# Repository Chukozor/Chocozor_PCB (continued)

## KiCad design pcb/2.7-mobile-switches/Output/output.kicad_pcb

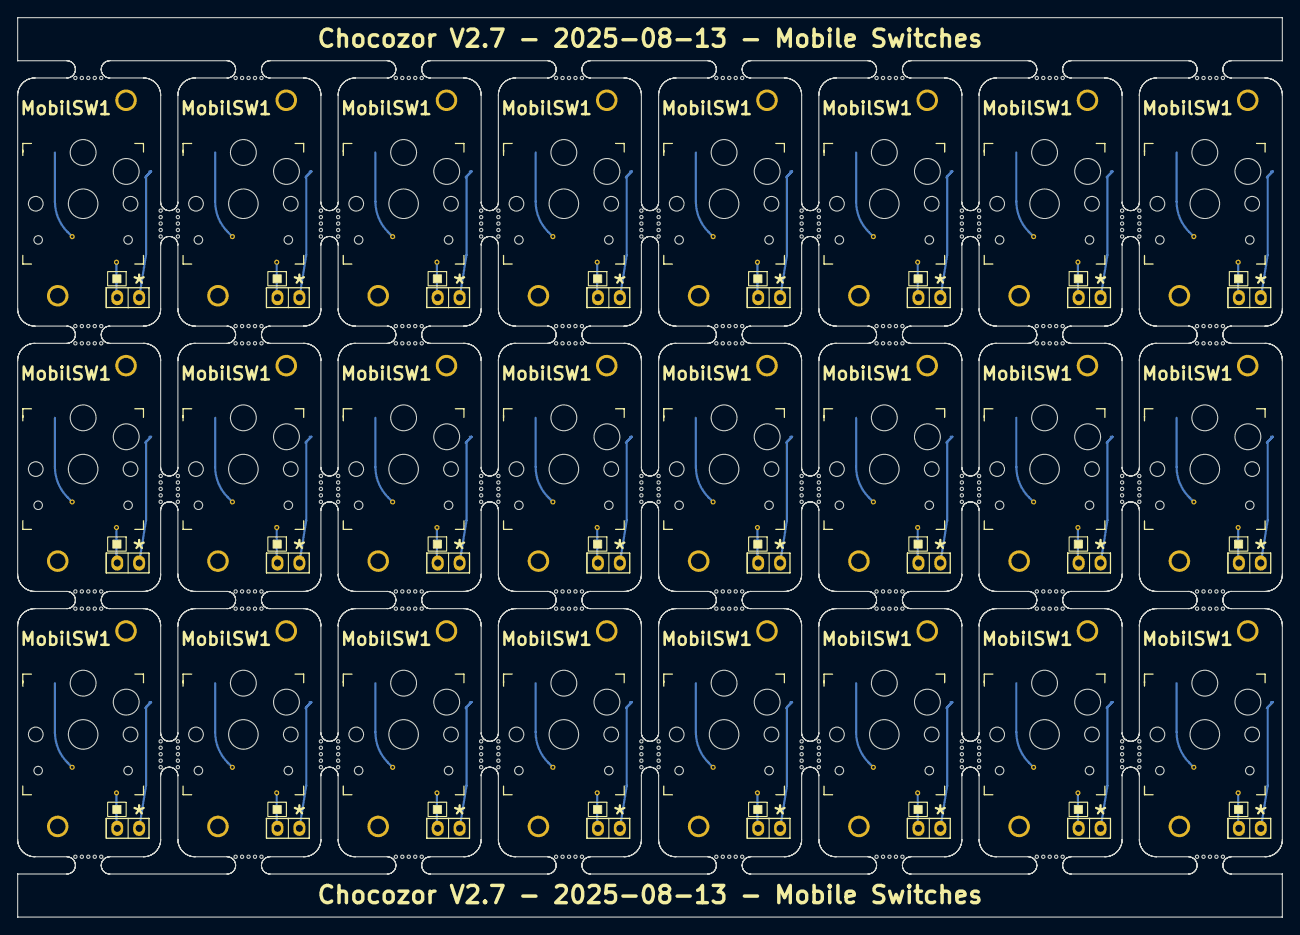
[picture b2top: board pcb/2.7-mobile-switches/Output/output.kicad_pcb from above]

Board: 2 copper layers, 146.8 x 104.4 mm, 570 parts (0 on the bottom side), 72 nets.

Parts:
D19, D19#2, D19#3, D19#4, D19#5, D19#6, D19#7, D19#8, D19#9, D19#10, D19#11, D19#12, D19#13, D19#14, D19#15, D19#16, D19#17, D19#18, D19#19, D19#20, D19#21, D19#22, D19#23, D19#24: 1N4148; SMD_SOD_123_only_one_face
HandSoldering2Pins-IN1, HandSoldering2Pins-IN1#2, HandSoldering2Pins-IN1#3, HandSoldering2Pins-IN1#4, HandSoldering2Pins-IN1#5, HandSoldering2Pins-IN1#6, HandSoldering2Pins-IN1#7, HandSoldering2Pins-IN1#8, HandSoldering2Pins-IN1#9, HandSoldering2Pins-IN1#10, HandSoldering2Pins-IN1#11, HandSoldering2Pins-IN1#12, HandSoldering2Pins-IN1#13, HandSoldering2Pins-IN1#14, HandSoldering2Pins-IN1#15, HandSoldering2Pins-IN1#16, HandSoldering2Pins-IN1#17, HandSoldering2Pins-IN1#18, HandSoldering2Pins-IN1#19, HandSoldering2Pins-IN1#20, HandSoldering2Pins-IN1#21, HandSoldering2Pins-IN1#22, HandSoldering2Pins-IN1#23, HandSoldering2Pins-IN1#24: Conn_01x02; HandSoldering-2pins-OUT
KiKit_MB_1_1, KiKit_MB_1_2, KiKit_MB_1_3, KiKit_MB_1_4, KiKit_MB_1_5, KiKit_MB_2_1, KiKit_MB_2_2, KiKit_MB_2_3, KiKit_MB_2_4, KiKit_MB_2_5, KiKit_MB_3_1, KiKit_MB_3_2, KiKit_MB_3_3, KiKit_MB_3_4, KiKit_MB_3_5, KiKit_MB_4_1, KiKit_MB_4_2, KiKit_MB_4_3, KiKit_MB_4_4, KiKit_MB_4_5, KiKit_MB_5_1, KiKit_MB_5_2, KiKit_MB_5_3, KiKit_MB_5_4, KiKit_MB_5_5, KiKit_MB_6_1, KiKit_MB_6_2, KiKit_MB_6_3, KiKit_MB_6_4, KiKit_MB_6_5, KiKit_MB_7_1, KiKit_MB_7_2, KiKit_MB_7_3, KiKit_MB_7_4, KiKit_MB_7_5, KiKit_MB_8_1, KiKit_MB_8_2, KiKit_MB_8_3, KiKit_MB_8_4, KiKit_MB_8_5, KiKit_MB_9_1, KiKit_MB_9_2, KiKit_MB_9_3, KiKit_MB_9_4, KiKit_MB_9_5, KiKit_MB_10_1, KiKit_MB_10_2, KiKit_MB_10_3, KiKit_MB_10_4, KiKit_MB_10_5, KiKit_MB_11_1, KiKit_MB_11_2, KiKit_MB_11_3, KiKit_MB_11_4, KiKit_MB_11_5, KiKit_MB_12_1, KiKit_MB_12_2, KiKit_MB_12_3, KiKit_MB_12_4, KiKit_MB_12_5, KiKit_MB_13_1, KiKit_MB_13_2, KiKit_MB_13_3, KiKit_MB_13_4, KiKit_MB_13_5, KiKit_MB_14_1, KiKit_MB_14_2, KiKit_MB_14_3, KiKit_MB_14_4, KiKit_MB_14_5, KiKit_MB_15_1, KiKit_MB_15_2, KiKit_MB_15_3, KiKit_MB_15_4, KiKit_MB_15_5, KiKit_MB_16_1, KiKit_MB_16_2, KiKit_MB_16_3, KiKit_MB_16_4, KiKit_MB_16_5, KiKit_MB_17_1, KiKit_MB_17_2, KiKit_MB_17_3, KiKit_MB_17_4, KiKit_MB_17_5, KiKit_MB_18_1, KiKit_MB_18_2, KiKit_MB_18_3, KiKit_MB_18_4, KiKit_MB_18_5, KiKit_MB_19_1, KiKit_MB_19_2, KiKit_MB_19_3, KiKit_MB_19_4, KiKit_MB_19_5, KiKit_MB_20_1, KiKit_MB_20_2, KiKit_MB_20_3, KiKit_MB_20_4, KiKit_MB_20_5, KiKit_MB_21_1, KiKit_MB_21_2, KiKit_MB_21_3, KiKit_MB_21_4, KiKit_MB_21_5, KiKit_MB_22_1, KiKit_MB_22_2, KiKit_MB_22_3, KiKit_MB_22_4, KiKit_MB_22_5, KiKit_MB_23_1, KiKit_MB_23_2, KiKit_MB_23_3, KiKit_MB_23_4, KiKit_MB_23_5, KiKit_MB_24_1, KiKit_MB_24_2, KiKit_MB_24_3, KiKit_MB_24_4, KiKit_MB_24_5, KiKit_MB_25_1, KiKit_MB_25_2, KiKit_MB_25_3, KiKit_MB_25_4, KiKit_MB_25_5, KiKit_MB_26_1, KiKit_MB_26_2, KiKit_MB_26_3, KiKit_MB_26_4, KiKit_MB_26_5, KiKit_MB_27_1, KiKit_MB_27_2, KiKit_MB_27_3, KiKit_MB_27_4, KiKit_MB_27_5, KiKit_MB_28_1, KiKit_MB_28_2, KiKit_MB_28_3, KiKit_MB_28_4, KiKit_MB_28_5, KiKit_MB_29_1, KiKit_MB_29_2, KiKit_MB_29_3, KiKit_MB_29_4, KiKit_MB_29_5, KiKit_MB_30_1, KiKit_MB_30_2, KiKit_MB_30_3, KiKit_MB_30_4, KiKit_MB_30_5, KiKit_MB_31_1, KiKit_MB_31_2, KiKit_MB_31_3, KiKit_MB_31_4, KiKit_MB_31_5, KiKit_MB_32_1, KiKit_MB_32_2, KiKit_MB_32_3, KiKit_MB_32_4, KiKit_MB_32_5, KiKit_MB_33_1, KiKit_MB_33_2, KiKit_MB_33_3, KiKit_MB_33_4, KiKit_MB_33_5, KiKit_MB_34_1, KiKit_MB_34_2, KiKit_MB_34_3, KiKit_MB_34_4, KiKit_MB_34_5, KiKit_MB_35_1, KiKit_MB_35_2, KiKit_MB_35_3, KiKit_MB_35_4, KiKit_MB_35_5, KiKit_MB_36_1, KiKit_MB_36_2, KiKit_MB_36_3, KiKit_MB_36_4, KiKit_MB_36_5, KiKit_MB_37_1, KiKit_MB_37_2, KiKit_MB_37_3, KiKit_MB_37_4, KiKit_MB_37_5, KiKit_MB_38_1, KiKit_MB_38_2, KiKit_MB_38_3, KiKit_MB_38_4, KiKit_MB_38_5, KiKit_MB_39_1, KiKit_MB_39_2, KiKit_MB_39_3, KiKit_MB_39_4, KiKit_MB_39_5, KiKit_MB_40_1, KiKit_MB_40_2, KiKit_MB_40_3, KiKit_MB_40_4, KiKit_MB_40_5, KiKit_MB_41_1, KiKit_MB_41_2, KiKit_MB_41_3, KiKit_MB_41_4, KiKit_MB_41_5, KiKit_MB_42_1, KiKit_MB_42_2, KiKit_MB_42_3, KiKit_MB_42_4, KiKit_MB_42_5, KiKit_MB_43_1, KiKit_MB_43_2, KiKit_MB_43_3, KiKit_MB_43_4, KiKit_MB_43_5, KiKit_MB_44_1, KiKit_MB_44_2, KiKit_MB_44_3, KiKit_MB_44_4, KiKit_MB_44_5, KiKit_MB_45_1, KiKit_MB_45_2, KiKit_MB_45_3, KiKit_MB_45_4, KiKit_MB_45_5, KiKit_MB_46_1, KiKit_MB_46_2, KiKit_MB_46_3, KiKit_MB_46_4, KiKit_MB_46_5, KiKit_MB_47_1, KiKit_MB_47_2, KiKit_MB_47_3, KiKit_MB_47_4, KiKit_MB_47_5, KiKit_MB_48_1, KiKit_MB_48_2, KiKit_MB_48_3, KiKit_MB_48_4, KiKit_MB_48_5, KiKit_MB_49_1, KiKit_MB_49_2, KiKit_MB_49_3, KiKit_MB_49_4, KiKit_MB_49_5, KiKit_MB_50_1, KiKit_MB_50_2, KiKit_MB_50_3, KiKit_MB_50_4, KiKit_MB_50_5, KiKit_MB_51_1, KiKit_MB_51_2, KiKit_MB_51_3, KiKit_MB_51_4, KiKit_MB_51_5, KiKit_MB_52_1, KiKit_MB_52_2, KiKit_MB_52_3, KiKit_MB_52_4, KiKit_MB_52_5, KiKit_MB_53_1, KiKit_MB_53_2, KiKit_MB_53_3, KiKit_MB_53_4, KiKit_MB_53_5, KiKit_MB_54_1, KiKit_MB_54_2, KiKit_MB_54_3, KiKit_MB_54_4, KiKit_MB_54_5, KiKit_MB_55_1, KiKit_MB_55_2, KiKit_MB_55_3, KiKit_MB_55_4, KiKit_MB_55_5, KiKit_MB_56_1, KiKit_MB_56_2, KiKit_MB_56_3, KiKit_MB_56_4, KiKit_MB_56_5, KiKit_MB_57_1, KiKit_MB_57_2, KiKit_MB_57_3, KiKit_MB_57_4, KiKit_MB_57_5, KiKit_MB_58_1, KiKit_MB_58_2, KiKit_MB_58_3, KiKit_MB_58_4, KiKit_MB_58_5, KiKit_MB_59_1, KiKit_MB_59_2, KiKit_MB_59_3, KiKit_MB_59_4, KiKit_MB_59_5, KiKit_MB_60_1, KiKit_MB_60_2, KiKit_MB_60_3, KiKit_MB_60_4, KiKit_MB_60_5, KiKit_MB_61_1, KiKit_MB_61_2, KiKit_MB_61_3, KiKit_MB_61_4, KiKit_MB_61_5, KiKit_MB_62_1, KiKit_MB_62_2, KiKit_MB_62_3, KiKit_MB_62_4, KiKit_MB_62_5, KiKit_MB_63_1, KiKit_MB_63_2, KiKit_MB_63_3, KiKit_MB_63_4, KiKit_MB_63_5, KiKit_MB_64_1, KiKit_MB_64_2, KiKit_MB_64_3, KiKit_MB_64_4, KiKit_MB_64_5, KiKit_MB_65_1, KiKit_MB_65_2, KiKit_MB_65_3, KiKit_MB_65_4, KiKit_MB_65_5, KiKit_MB_66_1, KiKit_MB_66_2, KiKit_MB_66_3, KiKit_MB_66_4, KiKit_MB_66_5, KiKit_MB_67_1, KiKit_MB_67_2, KiKit_MB_67_3, KiKit_MB_67_4, KiKit_MB_67_5, KiKit_MB_68_1, KiKit_MB_68_2, KiKit_MB_68_3, KiKit_MB_68_4, KiKit_MB_68_5, KiKit_MB_69_1, KiKit_MB_69_2, KiKit_MB_69_3, KiKit_MB_69_4, KiKit_MB_69_5, KiKit_MB_70_1, KiKit_MB_70_2, KiKit_MB_70_3, KiKit_MB_70_4, KiKit_MB_70_5, KiKit_MB_71_1, KiKit_MB_71_2, KiKit_MB_71_3, KiKit_MB_71_4, KiKit_MB_71_5, KiKit_MB_72_1, KiKit_MB_72_2, KiKit_MB_72_3, KiKit_MB_72_4, KiKit_MB_72_5, KiKit_MB_73_1, KiKit_MB_73_2, KiKit_MB_73_3, KiKit_MB_73_4, KiKit_MB_73_5, KiKit_MB_74_1, KiKit_MB_74_2, KiKit_MB_74_3, KiKit_MB_74_4, KiKit_MB_74_5, KiKit_MB_75_1, KiKit_MB_75_2, KiKit_MB_75_3, KiKit_MB_75_4, KiKit_MB_75_5, KiKit_MB_76_1, KiKit_MB_76_2, KiKit_MB_76_3, KiKit_MB_76_4, KiKit_MB_76_5, KiKit_MB_77_1, KiKit_MB_77_2, KiKit_MB_77_3, KiKit_MB_77_4, KiKit_MB_77_5, KiKit_MB_78_1, KiKit_MB_78_2, KiKit_MB_78_3, KiKit_MB_78_4, KiKit_MB_78_5, KiKit_MB_79_1, KiKit_MB_79_2, KiKit_MB_79_3, KiKit_MB_79_4, KiKit_MB_79_5, KiKit_MB_80_1, KiKit_MB_80_2, KiKit_MB_80_3, KiKit_MB_80_4, KiKit_MB_80_5, KiKit_MB_81_1, KiKit_MB_81_2, KiKit_MB_81_3, KiKit_MB_81_4, KiKit_MB_81_5, KiKit_MB_82_1, KiKit_MB_82_2, KiKit_MB_82_3, KiKit_MB_82_4, KiKit_MB_82_5, KiKit_MB_83_1, KiKit_MB_83_2, KiKit_MB_83_3, KiKit_MB_83_4, KiKit_MB_83_5, KiKit_MB_84_1, KiKit_MB_84_2, KiKit_MB_84_3, KiKit_MB_84_4, KiKit_MB_84_5, KiKit_MB_85_1, KiKit_MB_85_2, KiKit_MB_85_3, KiKit_MB_85_4, KiKit_MB_85_5, KiKit_MB_86_1, KiKit_MB_86_2, KiKit_MB_86_3, KiKit_MB_86_4, KiKit_MB_86_5, KiKit_MB_87_1, KiKit_MB_87_2, KiKit_MB_87_3, KiKit_MB_87_4, KiKit_MB_87_5, KiKit_MB_88_1, KiKit_MB_88_2, KiKit_MB_88_3, KiKit_MB_88_4, KiKit_MB_88_5, KiKit_MB_89_1, KiKit_MB_89_2, KiKit_MB_89_3, KiKit_MB_89_4, KiKit_MB_89_5, KiKit_MB_90_1, KiKit_MB_90_2, KiKit_MB_90_3, KiKit_MB_90_4, KiKit_MB_90_5: NPTH
M1.6-15, M1.6-15#2, M1.6-15#3, M1.6-15#4, M1.6-15#5, M1.6-15#6, M1.6-15#7, M1.6-15#8, M1.6-15#9, M1.6-15#10, M1.6-15#11, M1.6-15#12, M1.6-15#13, M1.6-15#14, M1.6-15#15, M1.6-15#16, M1.6-15#17, M1.6-15#18, M1.6-15#19, M1.6-15#20, M1.6-15#21, M1.6-15#22, M1.6-15#23, M1.6-15#24, M1.6-16, M1.6-16#2, M1.6-16#3, M1.6-16#4, M1.6-16#5, M1.6-16#6, M1.6-16#7, M1.6-16#8, M1.6-16#9, M1.6-16#10, M1.6-16#11, M1.6-16#12, M1.6-16#13, M1.6-16#14, M1.6-16#15, M1.6-16#16, M1.6-16#17, M1.6-16#18, M1.6-16#19, M1.6-16#20, M1.6-16#21, M1.6-16#22, M1.6-16#23, M1.6-16#24: MountingHoleM1.6; Mounting-hole-M1.6
MobilSW1, MobilSW1#2, MobilSW1#3, MobilSW1#4, MobilSW1#5, MobilSW1#6, MobilSW1#7, MobilSW1#8, MobilSW1#9, MobilSW1#10, MobilSW1#11, MobilSW1#12, MobilSW1#13, MobilSW1#14, MobilSW1#15, MobilSW1#16, MobilSW1#17, MobilSW1#18, MobilSW1#19, MobilSW1#20, MobilSW1#21, MobilSW1#22, MobilSW1#23, MobilSW1#24: Pull; Kailh_socket_PG1350_reversible_Chukozor_-PULL-simplifiev2

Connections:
Board_0-Net-(D19-A): D19#10.2 (A), MobilSW1#9.2
Board_0-Net-(D19-K): D19#10.1 (K), HandSoldering2Pins-IN1#15.2
Board_0-Net-(HandSoldering2Pins-IN1-Pin_1): HandSoldering2Pins-IN1#15.1, MobilSW1#9.1
Board_1-Net-(D19-A): D19#22.2 (A), MobilSW1#17.2
Board_1-Net-(D19-K): D19#22.1 (K), HandSoldering2Pins-IN1#8.2
Board_1-Net-(HandSoldering2Pins-IN1-Pin_1): HandSoldering2Pins-IN1#8.1, MobilSW1#17.1
Board_2-Net-(D19-A): D19#17.2 (A), MobilSW1#7.2
Board_2-Net-(D19-K): D19#17.1 (K), HandSoldering2Pins-IN1#6.2
Board_2-Net-(HandSoldering2Pins-IN1-Pin_1): HandSoldering2Pins-IN1#6.1, MobilSW1#7.1
Board_3-Net-(D19-A): D19#7.2 (A), MobilSW1#10.2
Board_3-Net-(D19-K): D19#7.1 (K), HandSoldering2Pins-IN1#7.2
Board_3-Net-(HandSoldering2Pins-IN1-Pin_1): HandSoldering2Pins-IN1#7.1, MobilSW1#10.1
Board_4-Net-(D19-A): D19#19.2 (A), MobilSW1#22.2
Board_4-Net-(D19-K): D19#19.1 (K), HandSoldering2Pins-IN1#13.2
Board_4-Net-(HandSoldering2Pins-IN1-Pin_1): HandSoldering2Pins-IN1#13.1, MobilSW1#22.1
Board_5-Net-(D19-A): D19#18.2 (A), MobilSW1#3.2
Board_5-Net-(D19-K): D19#18.1 (K), HandSoldering2Pins-IN1#9.2
Board_5-Net-(HandSoldering2Pins-IN1-Pin_1): HandSoldering2Pins-IN1#9.1, MobilSW1#3.1
Board_6-Net-(D19-A): D19#2.2 (A), MobilSW1#12.2
Board_6-Net-(D19-K): D19#2.1 (K), HandSoldering2Pins-IN1#19.2
Board_6-Net-(HandSoldering2Pins-IN1-Pin_1): HandSoldering2Pins-IN1#19.1, MobilSW1#12.1
Board_7-Net-(D19-A): D19#14.2 (A), MobilSW1#5.2
Board_7-Net-(D19-K): D19#14.1 (K), HandSoldering2Pins-IN1#23.2
Board_7-Net-(HandSoldering2Pins-IN1-Pin_1): HandSoldering2Pins-IN1#23.1, MobilSW1#5.1
Board_8-Net-(D19-A): D19#12.2 (A), MobilSW1#8.2
Board_8-Net-(D19-K): D19#12.1 (K), HandSoldering2Pins-IN1#24.2
Board_8-Net-(HandSoldering2Pins-IN1-Pin_1): HandSoldering2Pins-IN1#24.1, MobilSW1#8.1
Board_9-Net-(D19-A): D19#20.2 (A), MobilSW1#4.2
Board_9-Net-(D19-K): D19#20.1 (K), HandSoldering2Pins-IN1#5.2
Board_9-Net-(HandSoldering2Pins-IN1-Pin_1): HandSoldering2Pins-IN1#5.1, MobilSW1#4.1
Board_10-Net-(D19-A): D19#23.2 (A), MobilSW1.2
Board_10-Net-(D19-K): D19#23.1 (K), HandSoldering2Pins-IN1#16.2
Board_10-Net-(HandSoldering2Pins-IN1-Pin_1): HandSoldering2Pins-IN1#16.1, MobilSW1.1
Board_11-Net-(D19-A): D19#15.2 (A), MobilSW1#21.2
Board_11-Net-(D19-K): D19#15.1 (K), HandSoldering2Pins-IN1#21.2
Board_11-Net-(HandSoldering2Pins-IN1-Pin_1): HandSoldering2Pins-IN1#21.1, MobilSW1#21.1
Board_12-Net-(D19-A): D19#4.2 (A), MobilSW1#13.2
Board_12-Net-(D19-K): D19#4.1 (K), HandSoldering2Pins-IN1#22.2
Board_12-Net-(HandSoldering2Pins-IN1-Pin_1): HandSoldering2Pins-IN1#22.1, MobilSW1#13.1
Board_13-Net-(D19-A): D19.2 (A), MobilSW1#19.2
Board_13-Net-(D19-K): D19.1 (K), HandSoldering2Pins-IN1#11.2
Board_13-Net-(HandSoldering2Pins-IN1-Pin_1): HandSoldering2Pins-IN1#11.1, MobilSW1#19.1
Board_14-Net-(D19-A): D19#5.2 (A), MobilSW1#14.2
Board_14-Net-(D19-K): D19#5.1 (K), HandSoldering2Pins-IN1#20.2
Board_14-Net-(HandSoldering2Pins-IN1-Pin_1): HandSoldering2Pins-IN1#20.1, MobilSW1#14.1
Board_15-Net-(D19-A): D19#9.2 (A), MobilSW1#18.2
Board_15-Net-(D19-K): D19#9.1 (K), HandSoldering2Pins-IN1#4.2
Board_15-Net-(HandSoldering2Pins-IN1-Pin_1): HandSoldering2Pins-IN1#4.1, MobilSW1#18.1
Board_16-Net-(D19-A): D19#16.2 (A), MobilSW1#6.2
Board_16-Net-(D19-K): D19#16.1 (K), HandSoldering2Pins-IN1#3.2
Board_16-Net-(HandSoldering2Pins-IN1-Pin_1): HandSoldering2Pins-IN1#3.1, MobilSW1#6.1
Board_17-Net-(D19-A): D19#3.2 (A), MobilSW1#2.2
Board_17-Net-(D19-K): D19#3.1 (K), HandSoldering2Pins-IN1#12.2
Board_17-Net-(HandSoldering2Pins-IN1-Pin_1): HandSoldering2Pins-IN1#12.1, MobilSW1#2.1
Board_18-Net-(D19-A): D19#21.2 (A), MobilSW1#20.2
Board_18-Net-(D19-K): D19#21.1 (K), HandSoldering2Pins-IN1#14.2
Board_18-Net-(HandSoldering2Pins-IN1-Pin_1): HandSoldering2Pins-IN1#14.1, MobilSW1#20.1
Board_19-Net-(D19-A): D19#11.2 (A), MobilSW1#24.2
Board_19-Net-(D19-K): D19#11.1 (K), HandSoldering2Pins-IN1#17.2
Board_19-Net-(HandSoldering2Pins-IN1-Pin_1): HandSoldering2Pins-IN1#17.1, MobilSW1#24.1
Board_20-Net-(D19-A): D19#13.2 (A), MobilSW1#15.2
Board_20-Net-(D19-K): D19#13.1 (K), HandSoldering2Pins-IN1#18.2
Board_20-Net-(HandSoldering2Pins-IN1-Pin_1): HandSoldering2Pins-IN1#18.1, MobilSW1#15.1
Board_21-Net-(D19-A): D19#8.2 (A), MobilSW1#16.2
Board_21-Net-(D19-K): D19#8.1 (K), HandSoldering2Pins-IN1.2
Board_21-Net-(HandSoldering2Pins-IN1-Pin_1): HandSoldering2Pins-IN1.1, MobilSW1#16.1
Board_22-Net-(D19-A): D19#6.2 (A), MobilSW1#23.2
Board_22-Net-(D19-K): D19#6.1 (K), HandSoldering2Pins-IN1#2.2
Board_22-Net-(HandSoldering2Pins-IN1-Pin_1): HandSoldering2Pins-IN1#2.1, MobilSW1#23.1
Board_23-Net-(D19-A): D19#24.2 (A), MobilSW1#11.2
Board_23-Net-(D19-K): D19#24.1 (K), HandSoldering2Pins-IN1#10.2
Board_23-Net-(HandSoldering2Pins-IN1-Pin_1): HandSoldering2Pins-IN1#10.1, MobilSW1#11.1

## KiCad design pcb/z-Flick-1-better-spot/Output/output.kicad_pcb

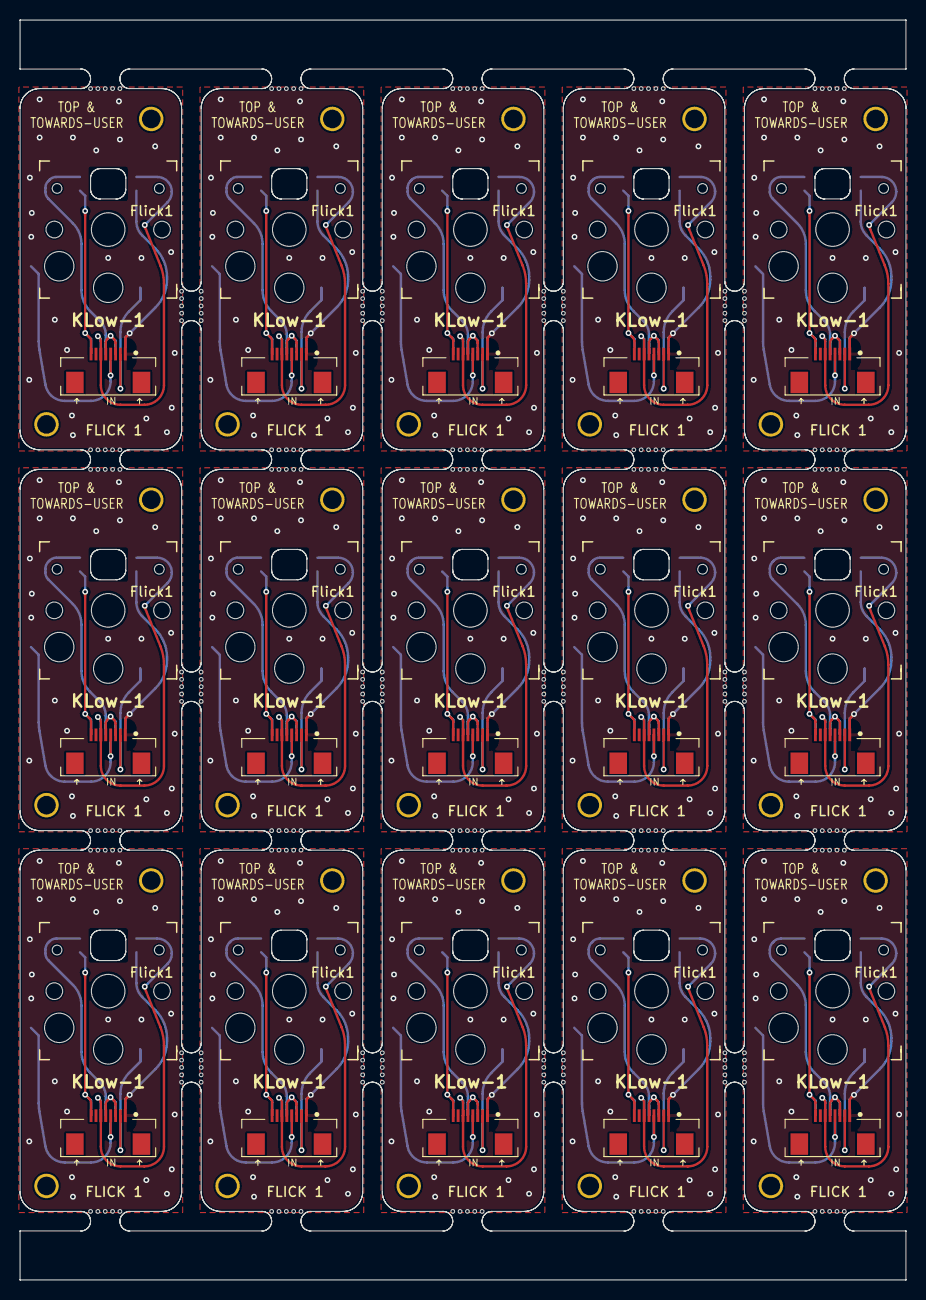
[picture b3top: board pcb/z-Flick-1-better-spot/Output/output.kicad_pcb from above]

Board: 2 copper layers, 90.5 x 128.7 mm, 330 parts (0 on the bottom side), 90 nets.

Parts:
Flick1, Flick1#2, Flick1#3, Flick1#4, Flick1#5, Flick1#6, Flick1#7, Flick1#8, Flick1#9, Flick1#10, Flick1#11, Flick1#12, Flick1#13, Flick1#14, Flick1#15: SW_Chuk; Kailh_socket_PG1350_reversible_Chukozor_LED_F-MOBILE
KLow-1, KLow-1#2, KLow-1#3, KLow-1#4, KLow-1#5, KLow-1#6, KLow-1#7, KLow-1#8, KLow-1#9, KLow-1#10, KLow-1#11, KLow-1#12, KLow-1#13, KLow-1#14, KLow-1#15: FPC_8pins_687108183722; FPC_8pins_687108183722_reversible-Mobile-IN-LOW-FROMBELOW_S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
KiKit_MB_1_1, KiKit_MB_1_2, KiKit_MB_1_3, KiKit_MB_1_4, KiKit_MB_1_5, KiKit_MB_2_1, KiKit_MB_2_2, KiKit_MB_2_3, KiKit_MB_2_4, KiKit_MB_2_5, KiKit_MB_3_1, KiKit_MB_3_2, KiKit_MB_3_3, KiKit_MB_3_4, KiKit_MB_3_5, KiKit_MB_4_1, KiKit_MB_4_2, KiKit_MB_4_3, KiKit_MB_4_4, KiKit_MB_4_5, KiKit_MB_5_1, KiKit_MB_5_2, KiKit_MB_5_3, KiKit_MB_5_4, KiKit_MB_5_5, KiKit_MB_6_1, KiKit_MB_6_2, KiKit_MB_6_3, KiKit_MB_6_4, KiKit_MB_6_5, KiKit_MB_7_1, KiKit_MB_7_2, KiKit_MB_7_3, KiKit_MB_7_4, KiKit_MB_7_5, KiKit_MB_8_1, KiKit_MB_8_2, KiKit_MB_8_3, KiKit_MB_8_4, KiKit_MB_8_5, KiKit_MB_9_1, KiKit_MB_9_2, KiKit_MB_9_3, KiKit_MB_9_4, KiKit_MB_9_5, KiKit_MB_10_1, KiKit_MB_10_2, KiKit_MB_10_3, KiKit_MB_10_4, KiKit_MB_10_5, KiKit_MB_11_1, KiKit_MB_11_2, KiKit_MB_11_3, KiKit_MB_11_4, KiKit_MB_11_5, KiKit_MB_12_1, KiKit_MB_12_2, KiKit_MB_12_3, KiKit_MB_12_4, KiKit_MB_12_5, KiKit_MB_13_1, KiKit_MB_13_2, KiKit_MB_13_3, KiKit_MB_13_4, KiKit_MB_13_5, KiKit_MB_14_1, KiKit_MB_14_2, KiKit_MB_14_3, KiKit_MB_14_4, KiKit_MB_14_5, KiKit_MB_15_1, KiKit_MB_15_2, KiKit_MB_15_3, KiKit_MB_15_4, KiKit_MB_15_5, KiKit_MB_16_1, KiKit_MB_16_2, KiKit_MB_16_3, KiKit_MB_16_4, KiKit_MB_16_5, KiKit_MB_17_1, KiKit_MB_17_2, KiKit_MB_17_3, KiKit_MB_17_4, KiKit_MB_17_5, KiKit_MB_18_1, KiKit_MB_18_2, KiKit_MB_18_3, KiKit_MB_18_4, KiKit_MB_18_5, KiKit_MB_19_1, KiKit_MB_19_2, KiKit_MB_19_3, KiKit_MB_19_4, KiKit_MB_19_5, KiKit_MB_20_1, KiKit_MB_20_2, KiKit_MB_20_3, KiKit_MB_20_4, KiKit_MB_20_5, KiKit_MB_21_1, KiKit_MB_21_2, KiKit_MB_21_3, KiKit_MB_21_4, KiKit_MB_21_5, KiKit_MB_22_1, KiKit_MB_22_2, KiKit_MB_22_3, KiKit_MB_22_4, KiKit_MB_22_5, KiKit_MB_23_1, KiKit_MB_23_2, KiKit_MB_23_3, KiKit_MB_23_4, KiKit_MB_23_5, KiKit_MB_24_1, KiKit_MB_24_2, KiKit_MB_24_3, KiKit_MB_24_4, KiKit_MB_24_5, KiKit_MB_25_1, KiKit_MB_25_2, KiKit_MB_25_3, KiKit_MB_25_4, KiKit_MB_25_5, KiKit_MB_26_1, KiKit_MB_26_2, KiKit_MB_26_3, KiKit_MB_26_4, KiKit_MB_26_5, KiKit_MB_27_1, KiKit_MB_27_2, KiKit_MB_27_3, KiKit_MB_27_4, KiKit_MB_27_5, KiKit_MB_28_1, KiKit_MB_28_2, KiKit_MB_28_3, KiKit_MB_28_4, KiKit_MB_28_5, KiKit_MB_29_1, KiKit_MB_29_2, KiKit_MB_29_3, KiKit_MB_29_4, KiKit_MB_29_5, KiKit_MB_30_1, KiKit_MB_30_2, KiKit_MB_30_3, KiKit_MB_30_4, KiKit_MB_30_5, KiKit_MB_31_1, KiKit_MB_31_2, KiKit_MB_31_3, KiKit_MB_31_4, KiKit_MB_31_5, KiKit_MB_32_1, KiKit_MB_32_2, KiKit_MB_32_3, KiKit_MB_32_4, KiKit_MB_32_5, KiKit_MB_33_1, KiKit_MB_33_2, KiKit_MB_33_3, KiKit_MB_33_4, KiKit_MB_33_5, KiKit_MB_34_1, KiKit_MB_34_2, KiKit_MB_34_3, KiKit_MB_34_4, KiKit_MB_34_5, KiKit_MB_35_1, KiKit_MB_35_2, KiKit_MB_35_3, KiKit_MB_35_4, KiKit_MB_35_5, KiKit_MB_36_1, KiKit_MB_36_2, KiKit_MB_36_3, KiKit_MB_36_4, KiKit_MB_36_5, KiKit_MB_37_1, KiKit_MB_37_2, KiKit_MB_37_3, KiKit_MB_37_4, KiKit_MB_37_5, KiKit_MB_38_1, KiKit_MB_38_2, KiKit_MB_38_3, KiKit_MB_38_4, KiKit_MB_38_5, KiKit_MB_39_1, KiKit_MB_39_2, KiKit_MB_39_3, KiKit_MB_39_4, KiKit_MB_39_5, KiKit_MB_40_1, KiKit_MB_40_2, KiKit_MB_40_3, KiKit_MB_40_4, KiKit_MB_40_5, KiKit_MB_41_1, KiKit_MB_41_2, KiKit_MB_41_3, KiKit_MB_41_4, KiKit_MB_41_5, KiKit_MB_42_1, KiKit_MB_42_2, KiKit_MB_42_3, KiKit_MB_42_4, KiKit_MB_42_5, KiKit_MB_43_1, KiKit_MB_43_2, KiKit_MB_43_3, KiKit_MB_43_4, KiKit_MB_43_5, KiKit_MB_44_1, KiKit_MB_44_2, KiKit_MB_44_3, KiKit_MB_44_4, KiKit_MB_44_5, KiKit_MB_45_1, KiKit_MB_45_2, KiKit_MB_45_3, KiKit_MB_45_4, KiKit_MB_45_5, KiKit_MB_46_1, KiKit_MB_46_2, KiKit_MB_46_3, KiKit_MB_46_4, KiKit_MB_46_5, KiKit_MB_47_1, KiKit_MB_47_2, KiKit_MB_47_3, KiKit_MB_47_4, KiKit_MB_47_5, KiKit_MB_48_1, KiKit_MB_48_2, KiKit_MB_48_3, KiKit_MB_48_4, KiKit_MB_48_5, KiKit_MB_49_1, KiKit_MB_49_2, KiKit_MB_49_3, KiKit_MB_49_4, KiKit_MB_49_5, KiKit_MB_50_1, KiKit_MB_50_2, KiKit_MB_50_3, KiKit_MB_50_4, KiKit_MB_50_5, KiKit_MB_51_1, KiKit_MB_51_2, KiKit_MB_51_3, KiKit_MB_51_4, KiKit_MB_51_5, KiKit_MB_52_1, KiKit_MB_52_2, KiKit_MB_52_3, KiKit_MB_52_4, KiKit_MB_52_5, KiKit_MB_53_1, KiKit_MB_53_2, KiKit_MB_53_3, KiKit_MB_53_4, KiKit_MB_53_5, KiKit_MB_54_1, KiKit_MB_54_2, KiKit_MB_54_3, KiKit_MB_54_4, KiKit_MB_54_5: NPTH
M1.6-3, M1.6-3#2, M1.6-3#3, M1.6-3#4, M1.6-3#5, M1.6-3#6, M1.6-3#7, M1.6-3#8, M1.6-3#9, M1.6-3#10, M1.6-3#11, M1.6-3#12, M1.6-3#13, M1.6-3#14, M1.6-3#15, M1.6-4, M1.6-4#2, M1.6-4#3, M1.6-4#4, M1.6-4#5, M1.6-4#6, M1.6-4#7, M1.6-4#8, M1.6-4#9, M1.6-4#10, M1.6-4#11, M1.6-4#12, M1.6-4#13, M1.6-4#14, M1.6-4#15: MountingHoleM1.6; Mounting-hole-M1.6

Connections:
Board_0-GND_mobile_Flick1: Flick1#12.5 (VSS), KLow-1#2.6 (GND)
Board_0-Net-(Flick1-DIN): Flick1#12.6 (DIN), KLow-1#2.3 (LED->)
Board_0-Net-(Flick1-DOUT): Flick1#12.4 (DOUT), KLow-1#2.4 (LED<-)
Board_0-Net-(Flick1-VDD): Flick1#12.3 (VDD), KLow-1#2.5 (VBUS)
Board_0-Net-(KLow-1-Col2Switch): Flick1#12.1, KLow-1#2.2 (Col2Switch)
Board_0-Net-(KLow-1-Diode2Switch): Flick1#12.2, KLow-1#2.1 (Diode2Switch)
Board_1-GND_mobile_Flick1: Flick1#3.5 (VSS), KLow-1#14.6 (GND)
Board_1-Net-(Flick1-DIN): Flick1#3.6 (DIN), KLow-1#14.3 (LED->)
Board_1-Net-(Flick1-DOUT): Flick1#3.4 (DOUT), KLow-1#14.4 (LED<-)
Board_1-Net-(Flick1-VDD): Flick1#3.3 (VDD), KLow-1#14.5 (VBUS)
Board_1-Net-(KLow-1-Col2Switch): Flick1#3.1, KLow-1#14.2 (Col2Switch)
Board_1-Net-(KLow-1-Diode2Switch): Flick1#3.2, KLow-1#14.1 (Diode2Switch)
Board_2-GND_mobile_Flick1: Flick1#4.5 (VSS), KLow-1.6 (GND)
Board_2-Net-(Flick1-DIN): Flick1#4.6 (DIN), KLow-1.3 (LED->)
Board_2-Net-(Flick1-DOUT): Flick1#4.4 (DOUT), KLow-1.4 (LED<-)
Board_2-Net-(Flick1-VDD): Flick1#4.3 (VDD), KLow-1.5 (VBUS)
Board_2-Net-(KLow-1-Col2Switch): Flick1#4.1, KLow-1.2 (Col2Switch)
Board_2-Net-(KLow-1-Diode2Switch): Flick1#4.2, KLow-1.1 (Diode2Switch)
Board_3-GND_mobile_Flick1: Flick1#7.5 (VSS), KLow-1#12.6 (GND)
Board_3-Net-(Flick1-DIN): Flick1#7.6 (DIN), KLow-1#12.3 (LED->)
Board_3-Net-(Flick1-DOUT): Flick1#7.4 (DOUT), KLow-1#12.4 (LED<-)
Board_3-Net-(Flick1-VDD): Flick1#7.3 (VDD), KLow-1#12.5 (VBUS)
Board_3-Net-(KLow-1-Col2Switch): Flick1#7.1, KLow-1#12.2 (Col2Switch)
Board_3-Net-(KLow-1-Diode2Switch): Flick1#7.2, KLow-1#12.1 (Diode2Switch)
Board_4-GND_mobile_Flick1: Flick1#6.5 (VSS), KLow-1#10.6 (GND)
Board_4-Net-(Flick1-DIN): Flick1#6.6 (DIN), KLow-1#10.3 (LED->)
Board_4-Net-(Flick1-DOUT): Flick1#6.4 (DOUT), KLow-1#10.4 (LED<-)
Board_4-Net-(Flick1-VDD): Flick1#6.3 (VDD), KLow-1#10.5 (VBUS)
Board_4-Net-(KLow-1-Col2Switch): Flick1#6.1, KLow-1#10.2 (Col2Switch)
Board_4-Net-(KLow-1-Diode2Switch): Flick1#6.2, KLow-1#10.1 (Diode2Switch)
Board_5-GND_mobile_Flick1: Flick1#10.5 (VSS), KLow-1#9.6 (GND)
Board_5-Net-(Flick1-DIN): Flick1#10.6 (DIN), KLow-1#9.3 (LED->)
Board_5-Net-(Flick1-DOUT): Flick1#10.4 (DOUT), KLow-1#9.4 (LED<-)
Board_5-Net-(Flick1-VDD): Flick1#10.3 (VDD), KLow-1#9.5 (VBUS)
Board_5-Net-(KLow-1-Col2Switch): Flick1#10.1, KLow-1#9.2 (Col2Switch)
Board_5-Net-(KLow-1-Diode2Switch): Flick1#10.2, KLow-1#9.1 (Diode2Switch)
Board_6-GND_mobile_Flick1: Flick1#2.5 (VSS), KLow-1#11.6 (GND)
Board_6-Net-(Flick1-DIN): Flick1#2.6 (DIN), KLow-1#11.3 (LED->)
Board_6-Net-(Flick1-DOUT): Flick1#2.4 (DOUT), KLow-1#11.4 (LED<-)
Board_6-Net-(Flick1-VDD): Flick1#2.3 (VDD), KLow-1#11.5 (VBUS)
Board_6-Net-(KLow-1-Col2Switch): Flick1#2.1, KLow-1#11.2 (Col2Switch)
Board_6-Net-(KLow-1-Diode2Switch): Flick1#2.2, KLow-1#11.1 (Diode2Switch)
Board_7-GND_mobile_Flick1: Flick1#13.5 (VSS), KLow-1#4.6 (GND)
Board_7-Net-(Flick1-DIN): Flick1#13.6 (DIN), KLow-1#4.3 (LED->)
Board_7-Net-(Flick1-DOUT): Flick1#13.4 (DOUT), KLow-1#4.4 (LED<-)
Board_7-Net-(Flick1-VDD): Flick1#13.3 (VDD), KLow-1#4.5 (VBUS)
Board_7-Net-(KLow-1-Col2Switch): Flick1#13.1, KLow-1#4.2 (Col2Switch)
Board_7-Net-(KLow-1-Diode2Switch): Flick1#13.2, KLow-1#4.1 (Diode2Switch)
Board_8-GND_mobile_Flick1: Flick1#9.5 (VSS), KLow-1#5.6 (GND)
Board_8-Net-(Flick1-DIN): Flick1#9.6 (DIN), KLow-1#5.3 (LED->)
Board_8-Net-(Flick1-DOUT): Flick1#9.4 (DOUT), KLow-1#5.4 (LED<-)
Board_8-Net-(Flick1-VDD): Flick1#9.3 (VDD), KLow-1#5.5 (VBUS)
Board_8-Net-(KLow-1-Col2Switch): Flick1#9.1, KLow-1#5.2 (Col2Switch)
Board_8-Net-(KLow-1-Diode2Switch): Flick1#9.2, KLow-1#5.1 (Diode2Switch)
Board_9-GND_mobile_Flick1: Flick1#5.5 (VSS), KLow-1#3.6 (GND)
Board_9-Net-(Flick1-DIN): Flick1#5.6 (DIN), KLow-1#3.3 (LED->)
Board_9-Net-(Flick1-DOUT): Flick1#5.4 (DOUT), KLow-1#3.4 (LED<-)
Board_9-Net-(Flick1-VDD): Flick1#5.3 (VDD), KLow-1#3.5 (VBUS)
Board_9-Net-(KLow-1-Col2Switch): Flick1#5.1, KLow-1#3.2 (Col2Switch)
Board_9-Net-(KLow-1-Diode2Switch): Flick1#5.2, KLow-1#3.1 (Diode2Switch)
Board_10-GND_mobile_Flick1: Flick1#15.5 (VSS), KLow-1#15.6 (GND)
Board_10-Net-(Flick1-DIN): Flick1#15.6 (DIN), KLow-1#15.3 (LED->)
Board_10-Net-(Flick1-DOUT): Flick1#15.4 (DOUT), KLow-1#15.4 (LED<-)
Board_10-Net-(Flick1-VDD): Flick1#15.3 (VDD), KLow-1#15.5 (VBUS)
Board_10-Net-(KLow-1-Col2Switch): Flick1#15.1, KLow-1#15.2 (Col2Switch)
Board_10-Net-(KLow-1-Diode2Switch): Flick1#15.2, KLow-1#15.1 (Diode2Switch)
Board_11-GND_mobile_Flick1: Flick1.5 (VSS), KLow-1#6.6 (GND)
Board_11-Net-(Flick1-DIN): Flick1.6 (DIN), KLow-1#6.3 (LED->)
Board_11-Net-(Flick1-DOUT): Flick1.4 (DOUT), KLow-1#6.4 (LED<-)
Board_11-Net-(Flick1-VDD): Flick1.3 (VDD), KLow-1#6.5 (VBUS)
Board_11-Net-(KLow-1-Col2Switch): Flick1.1, KLow-1#6.2 (Col2Switch)
Board_11-Net-(KLow-1-Diode2Switch): Flick1.2, KLow-1#6.1 (Diode2Switch)
Board_12-GND_mobile_Flick1: Flick1#8.5 (VSS), KLow-1#7.6 (GND)
Board_12-Net-(Flick1-DIN): Flick1#8.6 (DIN), KLow-1#7.3 (LED->)
Board_12-Net-(Flick1-DOUT): Flick1#8.4 (DOUT), KLow-1#7.4 (LED<-)
Board_12-Net-(Flick1-VDD): Flick1#8.3 (VDD), KLow-1#7.5 (VBUS)
Board_12-Net-(KLow-1-Col2Switch): Flick1#8.1, KLow-1#7.2 (Col2Switch)
Board_12-Net-(KLow-1-Diode2Switch): Flick1#8.2, KLow-1#7.1 (Diode2Switch)
Board_13-GND_mobile_Flick1: Flick1#11.5 (VSS), KLow-1#8.6 (GND)
Board_13-Net-(Flick1-DIN): Flick1#11.6 (DIN), KLow-1#8.3 (LED->)
Board_13-Net-(Flick1-DOUT): Flick1#11.4 (DOUT), KLow-1#8.4 (LED<-)
Board_13-Net-(Flick1-VDD): Flick1#11.3 (VDD), KLow-1#8.5 (VBUS)
Board_13-Net-(KLow-1-Col2Switch): Flick1#11.1, KLow-1#8.2 (Col2Switch)
Board_13-Net-(KLow-1-Diode2Switch): Flick1#11.2, KLow-1#8.1 (Diode2Switch)
Board_14-GND_mobile_Flick1: Flick1#14.5 (VSS), KLow-1#13.6 (GND)
Board_14-Net-(Flick1-DIN): Flick1#14.6 (DIN), KLow-1#13.3 (LED->)
Board_14-Net-(Flick1-DOUT): Flick1#14.4 (DOUT), KLow-1#13.4 (LED<-)
Board_14-Net-(Flick1-VDD): Flick1#14.3 (VDD), KLow-1#13.5 (VBUS)
Board_14-Net-(KLow-1-Col2Switch): Flick1#14.1, KLow-1#13.2 (Col2Switch)
Board_14-Net-(KLow-1-Diode2Switch): Flick1#14.2, KLow-1#13.1 (Diode2Switch)

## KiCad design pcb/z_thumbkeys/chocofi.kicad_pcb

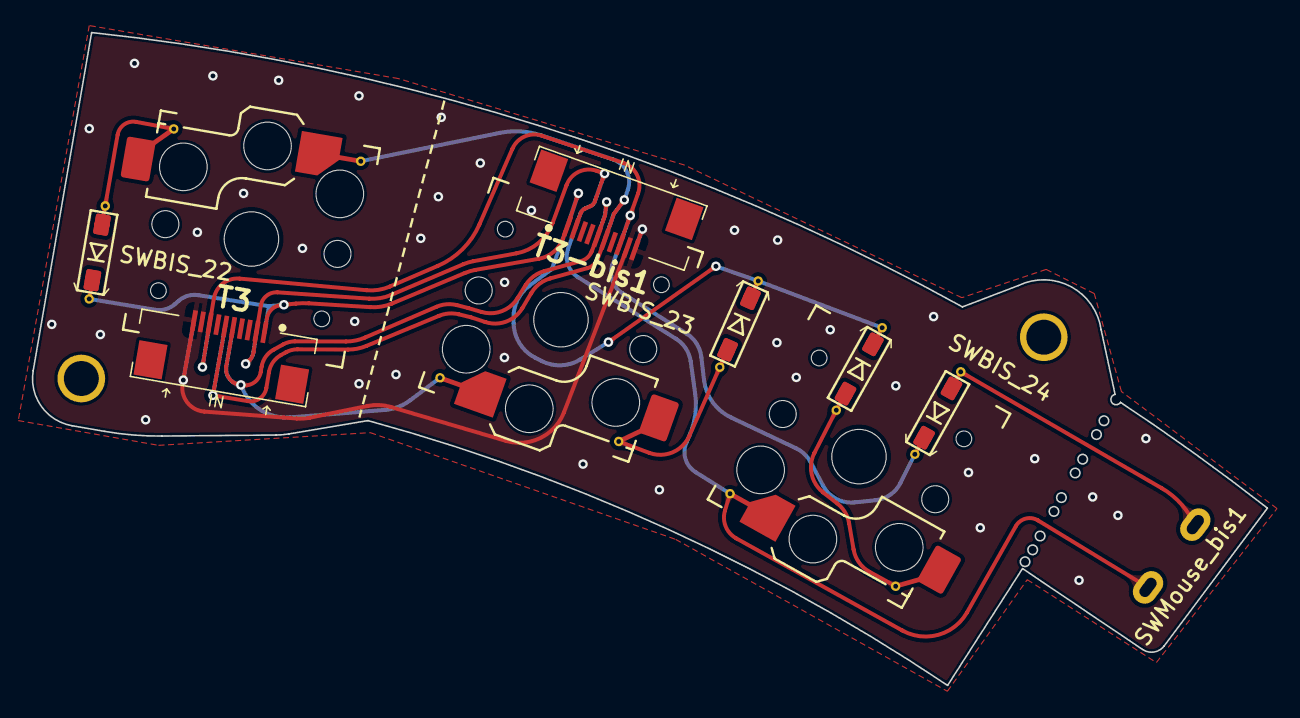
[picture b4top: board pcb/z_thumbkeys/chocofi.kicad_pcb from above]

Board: 2 copper layers, 77.8 x 41.1 mm, 12 parts (0 on the bottom side), 10 nets.

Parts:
D22b1, D23b1, D24b2, D31b1: 1N4148; SMD_SOD_123-stencil
M2-4, M2-5: MountingHoleM2; Mounting-hole-M2
SWBIS_22, SWBIS_23, SWBIS_24: Pull; Kailh_socket_PG1350_reversible_Chukozor_THUMBS_ext
SWMouse_bis1: CLIC; Microswitche-2pins
T3, T3-bis1: FPC_8pins_SPECIAL-thumbs; FPC_10p-reversible-ThumbORJoystick-IN

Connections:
GND-sep_thumbs: T3.9 (9_GND), T3.10 (10_GND), T3-bis1.9 (9_GND), T3-bis1.10 (10_GND)
unnamed: D22b1.2 (A), SWBIS_22.2
unnamed: D22b1.1 (K), D23b1.1 (K), D24b2.1 (K), T3.1 (1_ROW3), T3-bis1.1 (1_ROW3)
unnamed: D23b1.2 (A), SWBIS_23.2
unnamed: D24b2.2 (A), SWBIS_24.2
unnamed: D31b1.2 (A), SWMouse_bis1.2
unnamed: D31b1.1 (K), T3.8 (8_ROW5-(COM)), T3-bis1.8 (8_ROW5-(COM))
unnamed: SWBIS_24.1, SWMouse_bis1.1, T3.2 (2_COL5), T3-bis1.2 (2_COL5)
unnamed: SWBIS_23.1, T3.5 (5_COL4), T3-bis1.5 (5_COL4)
unnamed: SWBIS_22.1, T3.6 (6_COL3), T3-bis1.6 (6_COL3)

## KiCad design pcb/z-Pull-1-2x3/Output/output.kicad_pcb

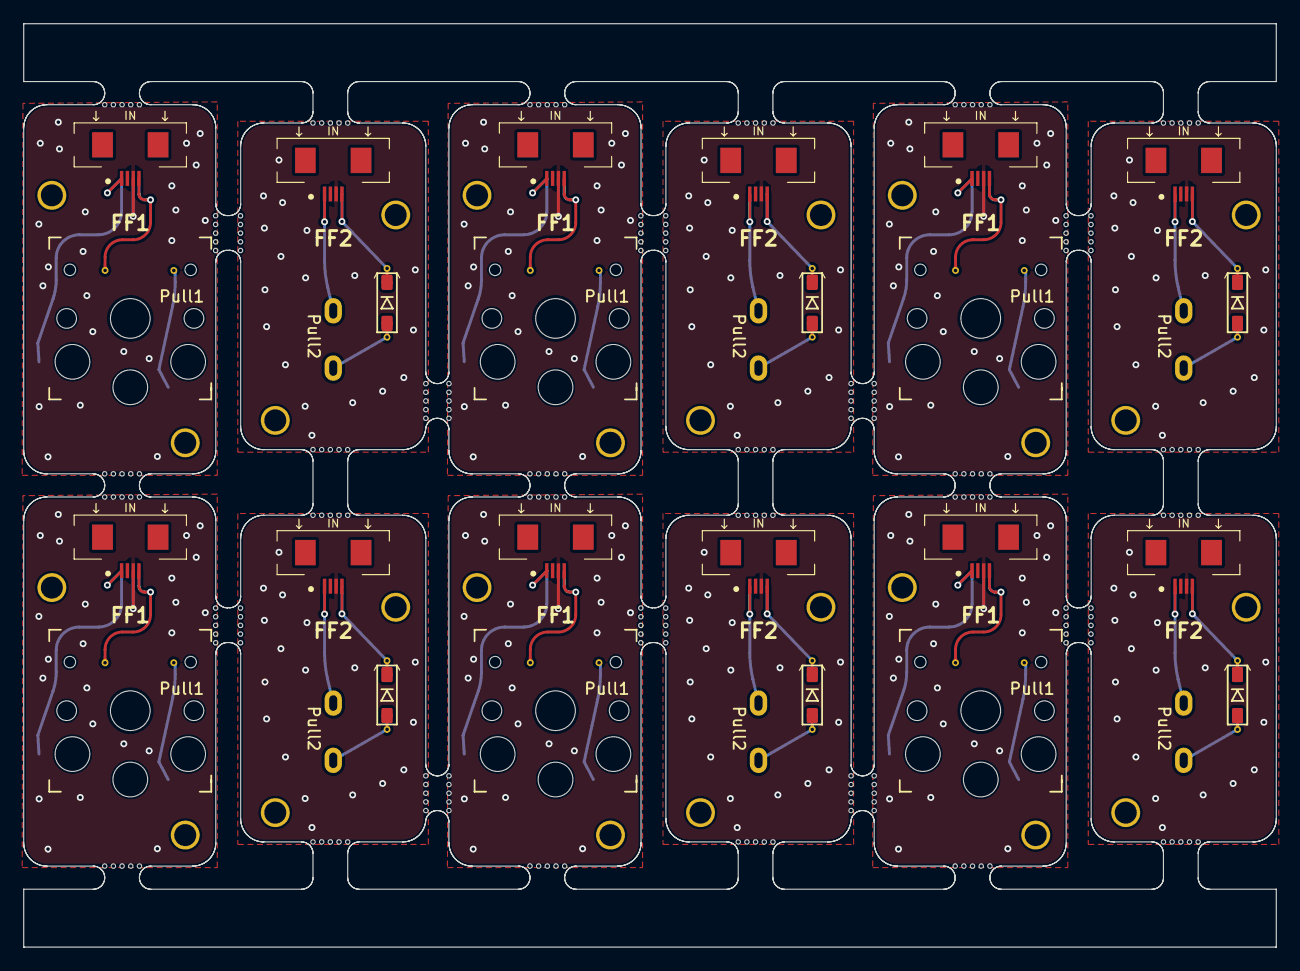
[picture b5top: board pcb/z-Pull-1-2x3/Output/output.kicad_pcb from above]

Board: 2 copper layers, 108.2 x 79.8 mm, 220 parts (0 on the bottom side), 36 nets.

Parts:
D33, D33#2, D33#3, D33#4, D33#5, D33#6: 1N4148; SMD_SOD_123_only_one_face
D34, D34#2, D34#3, D34#4, D34#5, D34#6: 1N4148; SMD_SOD_123-stencil
FF1, FF1#2, FF1#3, FF1#4, FF1#5, FF1#6, FF2, FF2#2, FF2#3, FF2#4, FF2#5, FF2#6: Conn_01x04; FPC_4pins_Horizontal-PULL-IN_stencil
KiKit_MB_1_1, KiKit_MB_1_2, KiKit_MB_1_3, KiKit_MB_1_4, KiKit_MB_1_5, KiKit_MB_2_1, KiKit_MB_2_2, KiKit_MB_2_3, KiKit_MB_2_4, KiKit_MB_2_5, KiKit_MB_3_1, KiKit_MB_3_2, KiKit_MB_3_3, KiKit_MB_3_4, KiKit_MB_3_5, KiKit_MB_4_1, KiKit_MB_4_2, KiKit_MB_4_3, KiKit_MB_4_4, KiKit_MB_4_5, KiKit_MB_5_1, KiKit_MB_5_2, KiKit_MB_5_3, KiKit_MB_5_4, KiKit_MB_5_5, KiKit_MB_6_1, KiKit_MB_6_2, KiKit_MB_6_3, KiKit_MB_6_4, KiKit_MB_6_5, KiKit_MB_7_1, KiKit_MB_7_2, KiKit_MB_7_3, KiKit_MB_7_4, KiKit_MB_7_5, KiKit_MB_8_1, KiKit_MB_8_2, KiKit_MB_8_3, KiKit_MB_8_4, KiKit_MB_8_5, KiKit_MB_9_1, KiKit_MB_9_2, KiKit_MB_9_3, KiKit_MB_9_4, KiKit_MB_9_5, KiKit_MB_10_1, KiKit_MB_10_2, KiKit_MB_10_3, KiKit_MB_10_4, KiKit_MB_10_5, KiKit_MB_11_1, KiKit_MB_11_2, KiKit_MB_11_3, KiKit_MB_11_4, KiKit_MB_11_5, KiKit_MB_12_1, KiKit_MB_12_2, KiKit_MB_12_3, KiKit_MB_12_4, KiKit_MB_12_5, KiKit_MB_13_1, KiKit_MB_13_2, KiKit_MB_13_3, KiKit_MB_13_4, KiKit_MB_13_5, KiKit_MB_14_1, KiKit_MB_14_2, KiKit_MB_14_3, KiKit_MB_14_4, KiKit_MB_14_5, KiKit_MB_15_1, KiKit_MB_15_2, KiKit_MB_15_3, KiKit_MB_15_4, KiKit_MB_15_5, KiKit_MB_16_1, KiKit_MB_16_2, KiKit_MB_16_3, KiKit_MB_16_4, KiKit_MB_16_5, KiKit_MB_17_1, KiKit_MB_17_2, KiKit_MB_17_3, KiKit_MB_17_4, KiKit_MB_17_5, KiKit_MB_18_1, KiKit_MB_18_2, KiKit_MB_18_3, KiKit_MB_18_4, KiKit_MB_18_5, KiKit_MB_19_1, KiKit_MB_19_2, KiKit_MB_19_3, KiKit_MB_19_4, KiKit_MB_19_5, KiKit_MB_20_1, KiKit_MB_20_2, KiKit_MB_20_3, KiKit_MB_20_4, KiKit_MB_20_5, KiKit_MB_21_1, KiKit_MB_21_2, KiKit_MB_21_3, KiKit_MB_21_4, KiKit_MB_21_5, KiKit_MB_22_1, KiKit_MB_22_2, KiKit_MB_22_3, KiKit_MB_22_4, KiKit_MB_22_5, KiKit_MB_23_1, KiKit_MB_23_2, KiKit_MB_23_3, KiKit_MB_23_4, KiKit_MB_23_5, KiKit_MB_24_1, KiKit_MB_24_2, KiKit_MB_24_3, KiKit_MB_24_4, KiKit_MB_24_5, KiKit_MB_25_1, KiKit_MB_25_2, KiKit_MB_25_3, KiKit_MB_25_4, KiKit_MB_25_5, KiKit_MB_26_1, KiKit_MB_26_2, KiKit_MB_26_3, KiKit_MB_26_4, KiKit_MB_26_5, KiKit_MB_27_1, KiKit_MB_27_2, KiKit_MB_27_3, KiKit_MB_27_4, KiKit_MB_27_5, KiKit_MB_28_1, KiKit_MB_28_2, KiKit_MB_28_3, KiKit_MB_28_4, KiKit_MB_28_5, KiKit_MB_29_1, KiKit_MB_29_2, KiKit_MB_29_3, KiKit_MB_29_4, KiKit_MB_29_5, KiKit_MB_30_1, KiKit_MB_30_2, KiKit_MB_30_3, KiKit_MB_30_4, KiKit_MB_30_5, KiKit_MB_31_1, KiKit_MB_31_2, KiKit_MB_31_3, KiKit_MB_31_4, KiKit_MB_31_5, KiKit_MB_32_1, KiKit_MB_32_2, KiKit_MB_32_3, KiKit_MB_32_4, KiKit_MB_32_5: NPTH
M1.6-1, M1.6-1#2, M1.6-1#3, M1.6-1#4, M1.6-1#5, M1.6-1#6, M1.6-2, M1.6-2#2, M1.6-2#3, M1.6-2#4, M1.6-2#5, M1.6-2#6, M1.6-11, M1.6-11#2, M1.6-11#3, M1.6-11#4, M1.6-11#5, M1.6-11#6, M1.6-12, M1.6-12#2, M1.6-12#3, M1.6-12#4, M1.6-12#5, M1.6-12#6: MountingHoleM1.6; Mounting-hole-M1.6
Pull1, Pull1#2, Pull1#3, Pull1#4, Pull1#5, Pull1#6: Pull; Kailh_socket_PG1350_reversible_Chukozor_-PULL-simplifiev2
Pull2, Pull2#2, Pull2#3, Pull2#4, Pull2#5, Pull2#6: Pull; Microswitche-2pins

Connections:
Board_0-Net-(D33-A): D33#2.2 (A), Pull1#5.2
Board_0-Net-(D33-K): D33#2.1 (K), FF1.4 (Pin_1)
Board_0-Net-(D34-A): D34#3.2 (A), Pull2#6.2
Board_0-Net-(D34-K): D34#3.1 (K), FF2#2.4 (Pin_1)
Board_0-Net-(FF1-Pin_4): FF1.1 (Pin_4), Pull1#5.1
Board_0-Net-(FF2-Pin_4): FF2#2.1 (Pin_4), Pull2#6.1
Board_1-Net-(D33-A): D33#6.2 (A), Pull1#3.2
Board_1-Net-(D33-K): D33#6.1 (K), FF1#4.4 (Pin_1)
Board_1-Net-(D34-A): D34.2 (A), Pull2#3.2
Board_1-Net-(D34-K): D34.1 (K), FF2#4.4 (Pin_1)
Board_1-Net-(FF1-Pin_4): FF1#4.1 (Pin_4), Pull1#3.1
Board_1-Net-(FF2-Pin_4): FF2#4.1 (Pin_4), Pull2#3.1
Board_2-Net-(D33-A): D33#3.2 (A), Pull1#6.2
Board_2-Net-(D33-K): D33#3.1 (K), FF1#5.4 (Pin_1)
Board_2-Net-(D34-A): D34#4.2 (A), Pull2#5.2
Board_2-Net-(D34-K): D34#4.1 (K), FF2#5.4 (Pin_1)
Board_2-Net-(FF1-Pin_4): FF1#5.1 (Pin_4), Pull1#6.1
Board_2-Net-(FF2-Pin_4): FF2#5.1 (Pin_4), Pull2#5.1
Board_3-Net-(D33-A): D33#5.2 (A), Pull1#4.2
Board_3-Net-(D33-K): D33#5.1 (K), FF1#6.4 (Pin_1)
Board_3-Net-(D34-A): D34#5.2 (A), Pull2#4.2
Board_3-Net-(D34-K): D34#5.1 (K), FF2#6.4 (Pin_1)
Board_3-Net-(FF1-Pin_4): FF1#6.1 (Pin_4), Pull1#4.1
Board_3-Net-(FF2-Pin_4): FF2#6.1 (Pin_4), Pull2#4.1
Board_4-Net-(D33-A): D33.2 (A), Pull1#2.2
Board_4-Net-(D33-K): D33.1 (K), FF1#2.4 (Pin_1)
Board_4-Net-(D34-A): D34#2.2 (A), Pull2#2.2
Board_4-Net-(D34-K): D34#2.1 (K), FF2.4 (Pin_1)
Board_4-Net-(FF1-Pin_4): FF1#2.1 (Pin_4), Pull1#2.1
Board_4-Net-(FF2-Pin_4): FF2.1 (Pin_4), Pull2#2.1
Board_5-Net-(D33-A): D33#4.2 (A), Pull1.2
Board_5-Net-(D33-K): D33#4.1 (K), FF1#3.4 (Pin_1)
Board_5-Net-(D34-A): D34#6.2 (A), Pull2.2
Board_5-Net-(D34-K): D34#6.1 (K), FF2#3.4 (Pin_1)
Board_5-Net-(FF1-Pin_4): FF1#3.1 (Pin_4), Pull1.1
Board_5-Net-(FF2-Pin_4): FF2#3.1 (Pin_4), Pull2.1
